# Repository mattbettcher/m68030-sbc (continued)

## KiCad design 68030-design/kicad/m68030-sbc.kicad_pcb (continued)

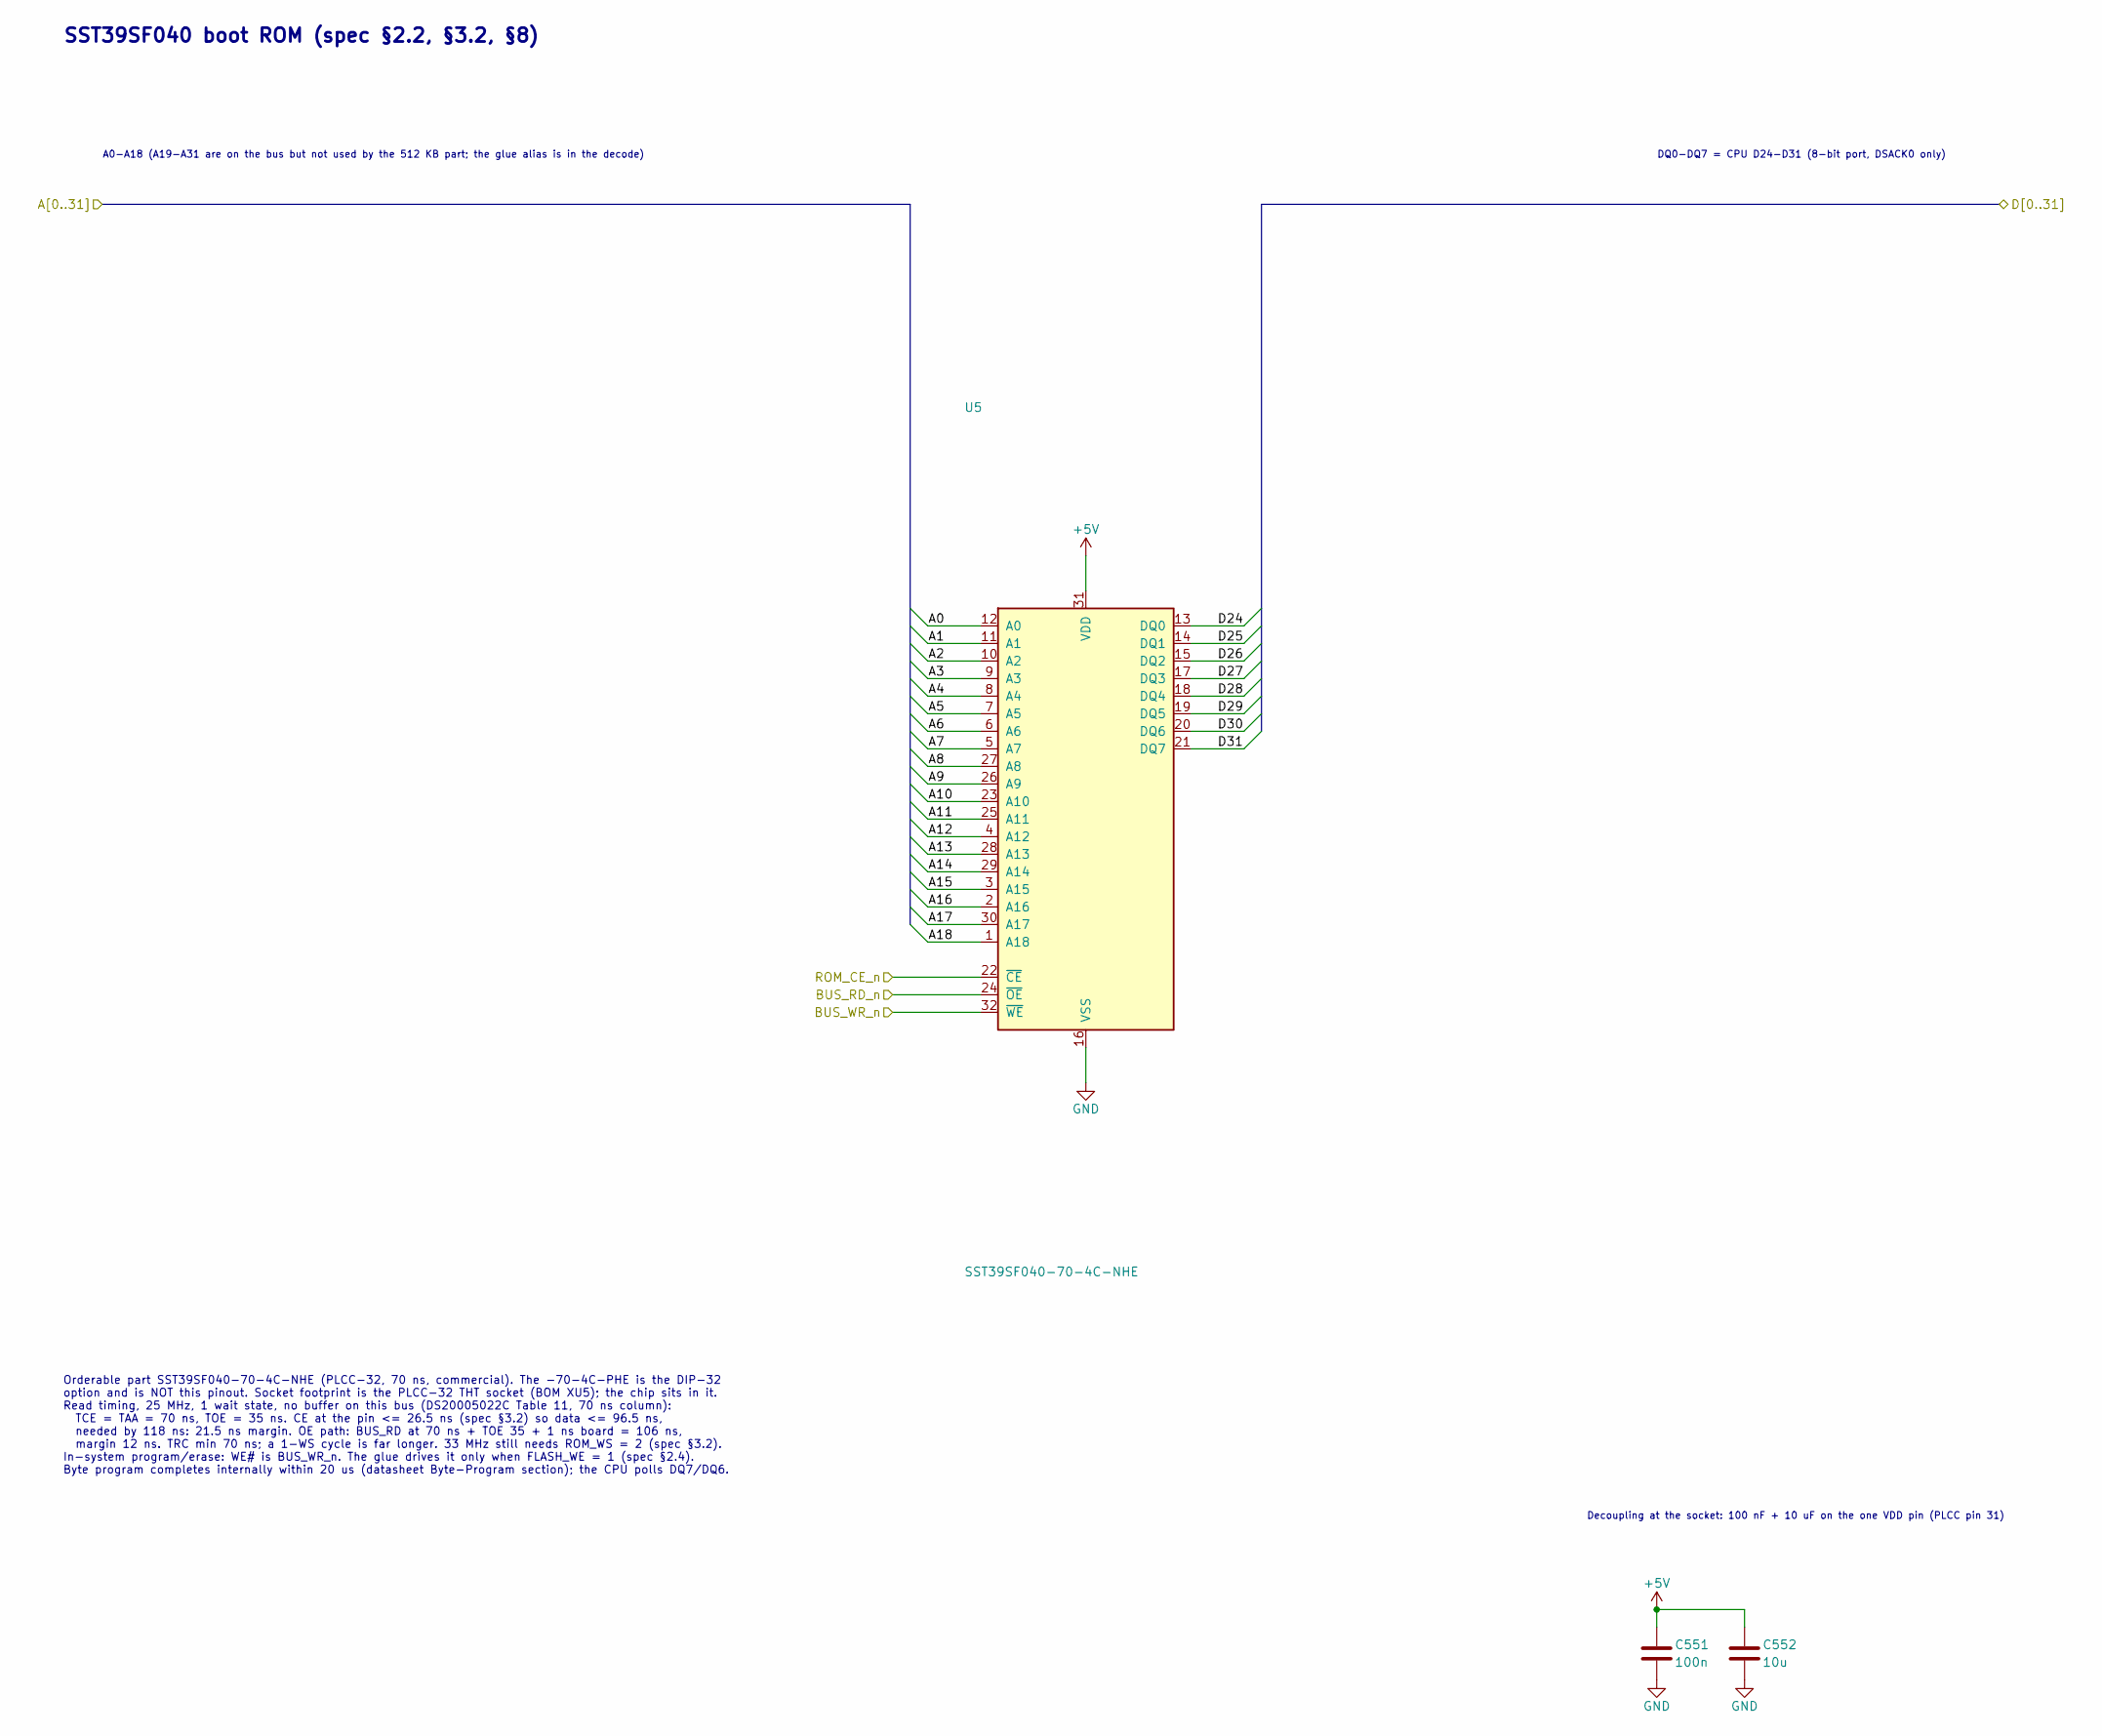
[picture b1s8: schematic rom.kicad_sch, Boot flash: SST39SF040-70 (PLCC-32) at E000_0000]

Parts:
C551: 100n; C_0805_2012Metric
C552: 10u; C_1206_3216Metric
U5: SST39SF040-70-4C-NHE; PLCC-32_THT-Socket; MPN SST39SF040-70-4C-NHE

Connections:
+5V: C551.1, C552.1, U5.31 (VDD); also elsewhere on the board
/A0: U5.12 (A0); also elsewhere on the board
/A1: U5.11 (A1); also elsewhere on the board
/A2: U5.10 (A2); also elsewhere on the board
/A3: U5.9 (A3); also elsewhere on the board
/A4: U5.8 (A4); also elsewhere on the board
/A5: U5.7 (A5); also elsewhere on the board
/A6: U5.6 (A6); also elsewhere on the board
/A7: U5.5 (A7); also elsewhere on the board
/A8: U5.27 (A8); also elsewhere on the board
/A9: U5.26 (A9); also elsewhere on the board
/A10: U5.23 (A10); also elsewhere on the board
/A11: U5.25 (A11); also elsewhere on the board
/A12: U5.4 (A12); also elsewhere on the board
/A13: U5.28 (A13); also elsewhere on the board
/A14: U5.29 (A14); also elsewhere on the board
/A15: U5.3 (A15); also elsewhere on the board
/A16: U5.2 (A16); also elsewhere on the board
/A17: U5.30 (A17); also elsewhere on the board
/A18: U5.1 (A18); also elsewhere on the board
/BUS_RD_n: U5.24 (~OE); also elsewhere on the board
/BUS_WR_n: U5.32 (~WE); also elsewhere on the board
/D24: U5.13 (DQ0); also elsewhere on the board
/D25: U5.14 (DQ1); also elsewhere on the board
/D26: U5.15 (DQ2); also elsewhere on the board
/D27: U5.17 (DQ3); also elsewhere on the board
/D28: U5.18 (DQ4); also elsewhere on the board
/D29: U5.19 (DQ5); also elsewhere on the board
/D30: U5.20 (DQ6); also elsewhere on the board
/D31: U5.21 (DQ7); also elsewhere on the board
/ROM_CE_n: U5.22 (~CE); also elsewhere on the board
GND: C551.2, C552.2, U5.16 (VSS); also elsewhere on the board

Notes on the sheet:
A0-A18 (A19-A31 are on the bus but not used by the 512 KB part; the glue alias is in the decode)
DQ0-DQ7 = CPU D24-D31 (8-bit port, DSACK0 only)
Decoupling at the socket: 100 nF + 10 uF on the one VDD pin (PLCC pin 31)
SST39SF040 boot ROM (spec §2.2, §3.2, §8)
Orderable part SST39SF040-70-4C-NHE (PLCC-32, 70 ns, commercial). The -70-4C-PHE is the DIP-32 option and is NOT this pinout. Socket footprint is the PLCC-32 THT socket (BOM XU5); the chip sits in it. Read timing, 25 MHz, 1 wait state, no buffer on this bus (DS20005022C Table 11, 70 ns column): TCE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

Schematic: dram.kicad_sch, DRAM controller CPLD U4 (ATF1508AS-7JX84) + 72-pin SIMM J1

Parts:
C801, C802, C803, C804, C805, C806, C807, C808, C810, C811, C812: 100n; C_0805_2012Metric
C809, C813, C814, C815: 10u; C_1206_3216Metric
C816, C817: 470u; CP_Radial_D10.0mm_P5.00mm
C818, C819, C820: 100n; C_0805_2012Metric; not fitted
J1: SIMM-72 socket; SIMM-72_TE-5822021-4; MPN TE 5822021-4
J5: JTAG U4 (ATDH1150USB); IDC-Header_2x05_P2.54mm_Vertical
JP801, JP802, JP803, JP804: open; SolderJumper-2_P1.3mm_Open_RoundedPad1.0x1.5mm
R801, R802, R803: 4.7k; R_0603_1608Metric
R804, R805, R806, R807, R808, R809, R810, R811, R812, R813, R814, R815, R816, R817, R818, R819, R820, R821, R822, R823, R824: 33; R_0603_1608Metric
R825, R826, R827, R828: 10k; R_0603_1608Metric
R829, R830, R831, R832, R833, R834, R835, R836, R837, R838: 33; R_0603_1608Metric; not fitted
TP801: RAS0#; TestPoint_Pad_D1.5mm
TP802: RAS1#; TestPoint_Pad_D1.5mm
TP803: CAS0#; TestPoint_Pad_D1.5mm
TP804: CAS1#; TestPoint_Pad_D1.5mm
TP805: CAS2#; TestPoint_Pad_D1.5mm
TP806: CAS3#; TestPoint_Pad_D1.5mm
TP807: WE#; TestPoint_Pad_D1.5mm
TP808: MUX_SEL; TestPoint_Pad_D1.5mm
TP809: U4-81; TestPoint_Pad_D1.5mm
U4: ATF1508AS-7JX84; PLCC-84_THT-Socket; MPN ATF1508AS-7JX84
U801, U802, U803: 74ACT257; SOIC-16_3.9x9.9mm_P1.27mm; MPN MC74ACT257DR2G; not fitted

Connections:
+5V: C801.1, C802.1, C803.1, C804.1, C805.1, C806.1, C807.1, C808.1, C809.1, C810.1, C811.1, C812.1, C813.1, C814.1, C815.1, C816.1, C817.1, C818.1, C819.1, C820.1, J1.10 (VDD), J1.30 (VDD), J1.59 (VDD), J5.4, R801.1, R802.1, R825.1, R826.1, R827.1, R828.1, U4.3 (VCCINT), U4.13 (VCCIO), U4.26 (VCCIO), U4.38 (VCCIO), U4.43 (VCCINT), U4.53 (VCCIO), U4.66 (VCCIO), U4.78 (VCCIO), U801.16 (VCC), U802.16 (VCC), U803.16 (VCC); also elsewhere on the board
/A0: U4.34 (I/O); also elsewhere on the board
/A1: U4.37 (I/O); also elsewhere on the board
/A2: U4.60 (I/O); also elsewhere on the board
/A3: U4.64 (I/O); also elsewhere on the board
/A4: U4.58 (I/O), U801.3 (I1a); also elsewhere on the board
/A5: U4.68 (I/O), U801.6 (I1b); also elsewhere on the board
/A6: U4.61 (I/O), U801.13 (I1c); also elsewhere on the board
/A7: U4.56 (I/O), U801.10 (I1d); also elsewhere on the board
/A8: U4.57 (I/O), U802.3 (I1a); also elsewhere on the board
/A9: U4.63 (I/O), U802.6 (I1b); also elsewhere on the board
/A10: U4.54 (I/O), U802.13 (I1c); also elsewhere on the board
/A11: U4.51 (I/O), U802.10 (I1d); also elsewhere on the board
/A12: U4.65 (I/O); also elsewhere on the board
/A13: U4.55 (I/O); also elsewhere on the board
/A14: U4.69 (I/O), U801.2 (I0a); also elsewhere on the board
/A15: U4.67 (I/O), U801.5 (I0b); also elsewhere on the board
/A16: U4.73 (I/O), U801.14 (I0c); also elsewhere on the board
/A17: U4.52 (I/O), U801.11 (I0d); also elsewhere on the board
/A18: U4.48 (I/O), U802.2 (I0a); also elsewhere on the board
/A19: U4.49 (I/O), U802.5 (I0b); also elsewhere on the board
/A20: U4.80 (I/O), U802.14 (I0c); also elsewhere on the board
/A21: U4.45 (I/O/PD2), U802.11 (I0d); also elsewhere on the board
/A22: U4.46 (I/O), U803.2 (I0a); also elsewhere on the board
/A23: U4.44 (I/O), U803.3 (I1a); also elsewhere on the board
/A24: U4.41 (I/O), U803.5 (I0b); also elsewhere on the board
/A25: U4.40 (I/O), U803.6 (I1b); also elsewhere on the board
/A26: U4.39 (I/O); also elsewhere on the board
/AS_n: U4.84 (INPUT/OE1); also elsewhere on the board
/CAS3_n: J1.42 (~CAS3), R823.2, TP806.1
/CBACK_n: JP803.1 (A); also elsewhere on the board
/CBREQ_n: JP802.1 (A); also elsewhere on the board
/CLK_DRAMC: U4.2 (INPUT/OE2/GCLK2); also elsewhere on the board
/D0: J1.2 (DQ1); also elsewhere on the board
/D1: J1.4 (DQ2); also elsewhere on the board
/D2: J1.6 (DQ3); also elsewhere on the board
/D3: J1.8 (DQ4); also elsewhere on the board
/D4: J1.20 (DQ5); also elsewhere on the board
/D5: J1.22 (DQ6); also elsewhere on the board
/D6: J1.24 (DQ7); also elsewhere on the board
/D7: J1.26 (DQ8); also elsewhere on the board
/D8: J1.49 (DQ9); also elsewhere on the board
/D9: J1.51 (DQ10); also elsewhere on the board
/D10: J1.53 (DQ11); also elsewhere on the board
/D11: J1.55 (DQ12); also elsewhere on the board
/D12: J1.57 (DQ13); also elsewhere on the board
/D13: J1.61 (DQ14); also elsewhere on the board
/D14: J1.63 (DQ15); also elsewhere on the board
/D15: J1.65 (DQ16); also elsewhere on the board
/D16: J1.3 (DQ17); also elsewhere on the board
/D17: J1.5 (DQ18); also elsewhere on the board
/D18: J1.7 (DQ19); also elsewhere on the board
/D19: J1.9 (DQ20); also elsewhere on the board
/D20: J1.21 (DQ21); also elsewhere on the board
/D21: J1.23 (DQ22); also elsewhere on the board
/D22: J1.25 (DQ23); also elsewhere on the board
/D23: J1.27 (DQ24); also elsewhere on the board
/D24: J1.50 (DQ25); also elsewhere on the board
/D25: J1.52 (DQ26); also elsewhere on the board
/D26: J1.54 (DQ27); also elsewhere on the board
/D27: J1.56 (DQ28); also elsewhere on the board
/D28: J1.58 (DQ29); also elsewhere on the board
/D29: J1.60 (DQ30); also elsewhere on the board
/D30: J1.62 (DQ31); also elsewhere on the board
/D31: J1.64 (DQ32); also elsewhere on the board
/DRAM_CLK: U4.83 (INPUT/GCLK1); also elsewhere on the board
/DRAM_SEL_n: U4.33 (I/O); also elsewhere on the board
/DSACK0_n: U4.28 (I/O); also elsewhere on the board
/DSACK1_n: U4.30 (I/O); also elsewhere on the board
/DS_n: JP804.2 (B); also elsewhere on the board
/PWR_RST_n: U4.1 (INPUT/GCLR); also elsewhere on the board
/RAS0_n: J1.44 (~RAS0), R816.2, TP801.1
/R_W: U4.31 (I/O); also elsewhere on the board
/SIMM_PD1: J1.67 (PRD1), R825.2; also elsewhere on the board
/SIMM_PD2: J1.68 (PRD2), R826.2; also elsewhere on the board
/SIMM_PD3: J1.69 (PRD3), R827.2; also elsewhere on the board
/SIMM_PD4: J1.70 (PRD4), R828.2; also elsewhere on the board
/SIZ0: U4.36 (I/O); also elsewhere on the board
/SIZ1: U4.35 (I/O); also elsewhere on the board
/STERM_n: JP801.1 (A); also elsewhere on the board
/WE_n: J1.47 (~WE), R824.2, TP807.1
/dram/CAS0_n: J1.40 (~CAS0), R820.2, TP803.1
/dram/CAS1_n: J1.43 (~CAS1), R821.2, TP804.1
/dram/CAS2_n: J1.41 (~CAS2), R822.2, TP805.1
/dram/MA0: J1.12 (A0), R804.2
/dram/MA1: J1.13 (A1), R805.2
/dram/MA2: J1.14 (A2), R806.2, R829.2
/dram/MA3: J1.15 (A3), R807.2, R830.2
/dram/MA4: J1.16 (A4), R808.2, R831.2
/dram/MA5: J1.17 (A5), R809.2, R832.2
/dram/MA6: J1.18 (A6), R810.2, R833.2
/dram/MA7: J1.28 (A7), R811.2, R834.2
/dram/MA8: J1.31 (A8), R812.2, R835.2
/dram/MA9: J1.32 (A9), R813.2, R836.2
/dram/MA10: J1.19 (A10), R814.2, R837.2
/dram/MA11: J1.29 (A11), R815.2, R838.2
/dram/MUX_SEL: TP808.1, U4.74 (I/O), U801.1 (S), U802.1 (S), U803.1 (S)
/dram/RAS1_n: J1.45 (~RAS1), R817.2, TP802.1
/dram/RAS2_n: J1.34 (~RAS2), R818.2
/dram/RAS3_n: J1.33 (~RAS3), R819.2
/dram/U4_CAS0_n: R820.1, U4.4 (I/O)
/dram/U4_CAS1_n: R821.1, U4.77 (I/O)
/dram/U4_CAS2_n: R822.1, U4.70 (I/O)
/dram/U4_CAS3_n: R823.1, U4.79 (I/O)
/dram/U4_MA0: R804.1, U4.22 (I/O)
/dram/U4_MA1: R805.1, U4.20 (I/O)
/dram/U4_MA2: R806.1, U4.25 (I/O)
/dram/U4_MA3: R807.1, U4.21 (I/O)
/dram/U4_MA4: R808.1, U4.24 (I/O)
/dram/U4_MA5: R809.1, U4.15 (I/O)
/dram/U4_MA6: R810.1, U4.12 (I/O/PD1)
/dram/U4_MA7: R811.1, U4.11 (I/O)
/dram/U4_MA8: R812.1, U4.27 (I/O)
/dram/U4_MA9: R813.1, U4.29 (I/O)
/dram/U4_MA10: R814.1, U4.10 (I/O)
/dram/U4_MA11: R815.1, U4.9 (I/O)
/dram/U4_RAS0_n: R816.1, U4.76 (I/O)
/dram/U4_RAS1_n: R817.1, U4.5 (I/O)
/dram/U4_RAS2_n: R818.1, U4.6 (I/O)
/dram/U4_RAS3_n: R819.1, U4.8 (I/O)
/dram/U4_SPARE81: TP809.1, U4.81 (I/O/GCLK3)
/dram/U4_TCK: J5.1, R803.1, U4.62 (I/O/TCK)
/dram/U4_TDI: J5.9, R802.2, U4.14 (I/O/TDI)
/dram/U4_TDO: J5.3, U4.71 (I/O/TDO)
/dram/U4_TMS: J5.5, R801.2, U4.23 (I/O/TMS)
/dram/U4_WE_n: R824.1, U4.75 (I/O)
GND: C801.2, C802.2, C803.2, C804.2, C805.2, C806.2, C807.2, C808.2, C809.2, C810.2, C811.2, C812.2, C813.2, C814.2, C815.2, C816.2, C817.2, C818.2, C819.2, C820.2, J1.1 (VSS), J1.39 (VSS), J1.72 (VSS), J5.2, J5.10, R803.2, U4.7 (GND), U4.19 (GND), U4.32 (GND), U4.42 (GND), U4.47 (GND), U4.59 (GND), U4.72 (GND), U4.82 (GND), U801.8 (GND), U801.15 (OE), U802.8 (GND), U802.15 (OE), U803.8 (GND), U803.10 (I1d), U803.11 (I0d), U803.13 (I1c), U803.14 (I0c), U803.15 (OE); also elsewhere on the board
unnamed: JP801.2 (B), U4.16 (I/O)
unnamed: JP802.2 (B), U4.17 (I/O)
unnamed: JP803.2 (B), U4.18 (I/O)
unnamed: JP804.1 (A), U4.50 (I/O)
unnamed: R829.1, U801.4 (Za)
unnamed: R830.1, U801.7 (Zb)
unnamed: R831.1, U801.12 (Zc)
unnamed: R832.1, U801.9 (Zd)
unnamed: R833.1, U802.4 (Za)
unnamed: R834.1, U802.7 (Zb)
unnamed: R835.1, U802.12 (Zc)
unnamed: R836.1, U802.9 (Zd)
unnamed: R837.1, U803.4 (Za)
unnamed: R838.1, U803.7 (Zb)

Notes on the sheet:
U4 address inputs A0-A26 are labelled A<n> (members of bus A[0..31])
U4 decoupling: 8x 100 nF, one at each VCC pin (VCCINT 3, 43; VCCIO 13, 26, 38, 53, 66, 78), + 10 uF bulk
Series terminations at U4 (spec 5.8)
33R, placed next to U4 (source termination)
R806-R815 (MA2-MA11): remove if the 74ACT257 fallback (U801-U803) is fitted
DQ1-DQ8 = D0-D7 (CAS0), DQ9-16 = D8-15 (CAS1), DQ17-24 = D16-23 (CAS2), DQ25-32 = D24-31 (CAS3)
SIMM presence detect (spec 5.1): 10k pull-ups; module ties PRDn to VSS or leaves it open. Read on DUART IP3-IP6 (advisory; firmware sizes by probing)
SIMM decoupling (spec 6.3): 100 nF + 10 uF at each VDD pin (10, 30, 59), 2x 470 uF low-ESR at the socket ends for the CBR refresh current spikes (all 16/32 DRAMs refresh at once)
Test points (SIMM side of the series resistors)
JTAG ISP header
J5: separate header for U4 (same pinout as J4 on the glue sheet; ATDH1150USB UG Table 1). Not chained with U3: the ATDH1150USB/ATMISP support multi-device chains, but a separate header lets each CPLD be programmed/recovered alone and a blank or damaged part cannot break the other's chain. R801/R802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
Fallback: external row/column address muxes (DNP)
Not needed: U4 fits with the MA mux inside (80/128 MC, 50 MHz met). To use: fit U801-U803 + C818-C820 and R829-R838, remove R806-R815 (U4 MA2-MA11 path), and rebuild dram.v with MA2-MA11 unused. S = MUX_SEL (U4 pin 74; low = row on I0, high = column on I1). 74ACT257 tpd <= 10.5 ns (onsemi MC74ACT25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
U801-U803 decoupling (DNP)
U4 DRAM controller + 72-pin SIMM (spec 3.2, 4.3, 5)
FITTED PINOUT: Yosys + hoglet67/atf15xx_yosys -> Microchip fit1508.exe v1918 (Wine), ATF1508AS PLCC84 -7, JTAG ON, pins locked (-preassign keep), -optimize on, -pin_keep on. Result: 80/128 macrocells, 52 flip-flops, 210 product terms; 55/60 user I/O + 4 JTAG + 3/4 dedicated inputs. Worst register-t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
Series resistors: 33R source termination on MA/RAS/CAS/WE. Trace Z0 ~50-60R minus the CPLD output impedance (~15-25R) [EST]; SIMM input loads (Micron): MA 48/95 pF, WE 64/127 pF, RAS 32 pF, CAS 16/32 pF (1/2-sided) -> 33R x 100 pF ~ 3.3 ns edge slowing, inside the DRAM timing margins (tRAH/tASC/tCA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

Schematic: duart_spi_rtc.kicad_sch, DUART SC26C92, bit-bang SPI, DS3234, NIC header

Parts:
BT1: CR2032; BatteryHolder_Keystone_3034_1x20mm; MPN Keystone 3034
C1001: 100n; C_0805_2012Metric
C1002: 10u; C_1206_3216Metric
C1003, C1004: 100n; C_0603_1608Metric
D6: OP6; LED_0805_2012Metric
J7, J8: TTL-232; PinHeader_1x06_P2.54mm_Vertical
J9: SPI NIC; PinHeader_2x05_P2.54mm_Vertical
R1001: 4.7k; R_0603_1608Metric
R1002, R1003, R1004, R1008: 10k; R_0603_1608Metric
R1005: 1.0k; R_0603_1608Metric
R1006: 2.2k; R_0603_1608Metric
R1007: 1k; R_0603_1608Metric
TP1001: OP7; TestPoint_Pad_D1.5mm
TP1002: RTC_INT; TestPoint_Pad_D1.5mm
U6: SC26C92A1A; PLCC-44_THT-Socket; MPN SC26C92A1A
U22: SN74LVC125ADR; SOIC-14_3.9x8.7mm_P1.27mm; MPN SN74LVC125ADR
U23: DS3234S#; SOIC-20W_7.5x12.8mm_P1.27mm; MPN DS3234S#

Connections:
+3V3: C1003.1, C1004.1, J9.1, R1004.1, R1008.1, U22.14 (VCC), U23.4 (VCC); also elsewhere on the board
+5V: C1001.1, C1002.1, J9.2, R1001.2, R1002.1, R1003.1, R1007.2, U6.44 (VCC); also elsewhere on the board
/A0: U6.2 (A0); also elsewhere on the board
/A1: U6.4 (A1); also elsewhere on the board
/A2: U6.6 (A2); also elsewhere on the board
/A3: U6.7 (A3); also elsewhere on the board
/BUS_RD_n: U6.10 (~RDN); also elsewhere on the board
/BUS_WR_n: U6.9 (~WRN); also elsewhere on the board
/D24: U6.28 (D0); also elsewhere on the board
/D25: U6.18 (D1); also elsewhere on the board
/D26: U6.27 (D2); also elsewhere on the board
/D27: U6.19 (D3); also elsewhere on the board
/D28: U6.26 (D4); also elsewhere on the board
/D29: U6.20 (D5); also elsewhere on the board
/D30: U6.25 (D6); also elsewhere on the board
/D31: U6.21 (D7); also elsewhere on the board
/DUART_CS_n: U6.39 (~CEN); also elsewhere on the board
/DUART_INT_n: R1001.1, U6.24 (~INTRN); also elsewhere on the board
/DUART_RST: U6.38 (RESET); also elsewhere on the board
/DUART_X1: U6.36 (X1); also elsewhere on the board
/DUART_X2: U6.37 (X2); also elsewhere on the board
/NIC_INT_n: J9.8, R1004.2; also elsewhere on the board
/PERIPH_RST_n: R1005.1; also elsewhere on the board
/SIMM_PD1: U6.3 (IP3); also elsewhere on the board
/SIMM_PD2: U6.43 (IP4); also elsewhere on the board
/SIMM_PD3: U6.42 (IP5); also elsewhere on the board
/SIMM_PD4: U6.41 (IP6); also elsewhere on the board
/SPI_HW_MISO: J9.6, U6.40 (IP2), U23.19 (DOUT); also elsewhere on the board
/SPI_HW_MOSI: U6.15 (OP3), U22.5; also elsewhere on the board
/SPI_HW_SCK: U6.31 (OP2), U22.2; also elsewhere on the board
/duart_spi_rtc/CTSA: J7.6, U6.8 (IP0)
/duart_spi_rtc/CTSB: J8.6, U6.5 (IP1)
/duart_spi_rtc/NIC_RST: J9.9, R1005.2, R1006.1
/duart_spi_rtc/OP6: D6.1 (K), U6.29 (OP6)
/duart_spi_rtc/OP7: TP1001.1, U6.17 (OP7)
/duart_spi_rtc/RTC_INT: R1008.2, TP1002.1, U23.5 (INT/SQW)
/duart_spi_rtc/RTSA: J7.2, U6.32 (OP0)
/duart_spi_rtc/RTSB: J8.2, U6.14 (OP1)
/duart_spi_rtc/RXDA: J7.4, U6.35 (RxDA)
/duart_spi_rtc/RXDB: J8.4, U6.11 (RxDB)
/duart_spi_rtc/SPI_CS0_5: R1002.2, U6.30 (OP4), U22.9
/duart_spi_rtc/SPI_CS1_5: R1003.2, U6.16 (OP5), U22.12
/duart_spi_rtc/SPI_CS_NIC: J9.7, U22.8
/duart_spi_rtc/SPI_CS_RTC: U22.11, U23.1 (~CS)
/duart_spi_rtc/SPI_MOSI: J9.5, U22.6, U23.17 (DIN)
/duart_spi_rtc/SPI_SCK: J9.4, U22.3, U23.18 (SCLK), U23.20 (SCLK)
/duart_spi_rtc/TXDA: J7.5, U6.33 (TxDA)
/duart_spi_rtc/TXDB: J8.5, U6.13 (TxDB)
/duart_spi_rtc/VBAT: BT1.1 (+), U23.16 (VBAT)
GND: BT1.2 (-), C1001.2, C1002.2, C1003.2, C1004.2, J7.1, J8.1, J9.3, J9.10, R1006.2, U6.22 (VSS), U22.1, U22.4, U22.7 (GND), U22.10, U22.13, U23.2 (NC), U23.7 (NC), U23.8 (NC), U23.9 (NC), U23.10 (NC), U23.11 (NC), U23.12 (NC), U23.13 (NC), U23.14 (NC), U23.15 (GND); also elsewhere on the board
unnamed: D6.2 (A), R1007.1

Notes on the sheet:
A0-A3 only (reg_shift = 0)
D0-D7 = CPU D24-D31
U6 decoupling (one VCC pin, PLCC pin 44)
SC26C92A1A (spec §8.3). Kept. 2 wait states still hold; glue not refit.
J7/J8 TTL-232: 1 GND, 2 CTS from our RTS, 3 cable VCC left open, 4 TXD to our RX, 5 RXD from our TX, 6 RTS to our CTS.
J9 pins: 1 +3V3, 2 +5V, 3 GND, 4 SCK, 5 MOSI, 6 MISO, 7 CS, 8 INT, 9 RST, 10 GND. SPI is 3.3 V.

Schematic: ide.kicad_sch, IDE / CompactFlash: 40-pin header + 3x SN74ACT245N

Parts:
C911, C912, C913: 100n; C_0805_2012Metric
D5: IDE; LED_0805_2012Metric
J6: IDE 40-pin; IDC-Header_2x20_P2.54mm_Vertical; MPN Wurth 61204021621
R901: 4.7k; R_0603_1608Metric
R902, R903, R905: 10k; R_0603_1608Metric
R904: 5.6k; R_0603_1608Metric
R906: 1k; R_0603_1608Metric
R911, R912, R913, R914, R915, R916, R917, R918: 33; R_0603_1608Metric
U11, U12, U13: SN74ACT245DW; SOIC-20W_7.5x12.8mm_P1.27mm; MPN SN74ACT245DW

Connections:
+5V: C911.1, C912.1, C913.1, R901.1, R905.1, R906.2, U11.20 (VCC), U12.20 (VCC), U13.1 (A->B), U13.20 (VCC); also elsewhere on the board
/D16: U12.18 (B0); also elsewhere on the board
/D17: U12.17 (B1); also elsewhere on the board
/D18: U12.16 (B2); also elsewhere on the board
/D19: U12.15 (B3); also elsewhere on the board
/D20: U12.14 (B4); also elsewhere on the board
/D21: U12.13 (B5); also elsewhere on the board
/D22: U12.12 (B6); also elsewhere on the board
/D23: U12.11 (B7); also elsewhere on the board
/D24: U11.18 (B0); also elsewhere on the board
/D25: U11.17 (B1); also elsewhere on the board
/D26: U11.16 (B2); also elsewhere on the board
/D27: U11.15 (B3); also elsewhere on the board
/D28: U11.14 (B4); also elsewhere on the board
/D29: U11.13 (B5); also elsewhere on the board
/D30: U11.12 (B6); also elsewhere on the board
/D31: U11.11 (B7); also elsewhere on the board
/IDE_BUF_EN_n: U11.19 (CE), U12.19 (CE); also elsewhere on the board
/IDE_CS0_n: U13.5 (A3); also elsewhere on the board
/IDE_CS1_n: U13.6 (A4); also elsewhere on the board
/IDE_DA0: U13.2 (A0); also elsewhere on the board
/IDE_DA1: U13.3 (A1); also elsewhere on the board
/IDE_DA2: U13.4 (A2); also elsewhere on the board
/IDE_DIOR_n: U13.7 (A5); also elsewhere on the board
/IDE_DIOW_n: U13.8 (A6); also elsewhere on the board
/IDE_INTRQ: J6.31, R903.1; also elsewhere on the board
/IDE_IORDY: J6.27, R901.2; also elsewhere on the board
/PERIPH_RST_n: U13.9 (A7); also elsewhere on the board
/R_W: U11.1 (A->B), U12.1 (A->B); also elsewhere on the board
/ide/CS0_n: J6.37, R914.2
/ide/CS1_n: J6.38, R915.2
/ide/DA0: J6.35, R911.2
/ide/DA1: J6.33, R912.2
/ide/DA2: J6.36, R913.2
/ide/DASP_n: D5.1 (K), J6.39
/ide/DD0: J6.17, U11.2 (A0)
/ide/DD1: J6.15, U11.3 (A1)
/ide/DD2: J6.13, U11.4 (A2)
/ide/DD3: J6.11, U11.5 (A3)
/ide/DD4: J6.9, U11.6 (A4)
/ide/DD5: J6.7, U11.7 (A5)
/ide/DD6: J6.5, U11.8 (A6)
/ide/DD7: J6.3, R902.1, U11.9 (A7)
/ide/DD8: J6.4, U12.2 (A0)
/ide/DD9: J6.6, U12.3 (A1)
/ide/DD10: J6.8, U12.4 (A2)
/ide/DD11: J6.10, U12.5 (A3)
/ide/DD12: J6.12, U12.6 (A4)
/ide/DD13: J6.14, U12.7 (A5)
/ide/DD14: J6.16, U12.8 (A6)
/ide/DD15: J6.18, U12.9 (A7)
/ide/DIOR_n: J6.25, R916.2
/ide/DIOW_n: J6.23, R917.2
/ide/DMACK_n: J6.29, R905.2
/ide/DMARQ: J6.21, R904.1
/ide/RESET_n: J6.1, R918.2
GND: C911.2, C912.2, C913.2, J6.2, J6.19, J6.22, J6.24, J6.26, J6.28, J6.30, J6.40, R902.2, R903.2, R904.2, U11.10 (GND), U12.10 (GND), U13.10 (GND), U13.19 (CE); also elsewhere on the board
unnamed: D5.2 (A), R906.1
unnamed: R911.1, U13.18 (B0)
unnamed: R912.1, U13.17 (B1)
unnamed: R913.1, U13.16 (B2)
unnamed: R914.1, U13.15 (B3)
unnamed: R915.1, U13.14 (B4)
unnamed: R916.1, U13.13 (B5)
unnamed: R917.1, U13.12 (B6)
unnamed: R918.1, U13.11 (B7)

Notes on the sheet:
D24-D31 (U11) and D16-D23 (U12) are members of D[0..31]. DIR = R/W high drives DD onto the CPU.
U13 is wired one way: DIR = +5V (A->B), OE = GND. DA2:0 are U3 pins 50-52, registered (glue Rev A.1).
U11 / U12 / U13 decoupling
IDE header (spec §1.2, §3.2). A CF-to-40-pin adapter uses this connector; no separate CF socket.
Terminations, ATA/ATAPI-6 (T13/1410D) §4.2.1 Table 5, notes 3, 4, 5, 7, 10: R901 4.7k IORDY pull-up to +5V (table value; note 10 allows 1k, not used). R902 10k DD7 pull-down (note 3: host shall pull DD7 down, not up). R903 10k INTRQ pull-down (note 5; spec §3.5: active high). R904 5.6k DMARQ pull-d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
PIO-0 vs SN74ACT245N (SCAS452H Fig. 6-1, CL = 50 pF only; no 150 pF number). SN74, VCC 5 V +/- 0.5 V, over temperature: tPLH 1.5 to 8 ns, tPHL 1 to 9 ns. 13 WS unchanged. At the drive: t0 631 ns (margin 31), t1 111.7 (42), t2 352.5 (62 vs 290), t4 50 (20), t9 36.6 (17). Read t5 misses: DIOR tPLH an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

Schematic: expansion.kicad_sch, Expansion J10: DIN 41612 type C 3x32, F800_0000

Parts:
C1401, C1402, C1403, C1404, C1405, C1406, C1407, C1408: 100n; C_0805_2012Metric
C1409: 10u; C_1206_3216Metric
J10: DIN41612-C-96; DIN41612_C_3x32_Female_Vertical_THT; MPN HARTING 09032966821
U14, U15, U16, U17: SN74ACT244DW; SOIC-20W_7.5x12.8mm_P1.27mm; MPN SN74ACT244DW
U18, U19, U20, U21: SN74ACT245DW; SOIC-20W_7.5x12.8mm_P1.27mm; MPN SN74ACT245DW

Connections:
+5V: C1401.1, C1402.1, C1403.1, C1404.1, C1405.1, C1406.1, C1407.1, C1408.1, C1409.1, J10.c21, J10.c22, J10.c23, J10.c24, U14.20 (VCC), U15.20 (VCC), U16.20 (VCC), U17.20 (VCC), U18.20 (VCC), U19.20 (VCC), U20.20 (VCC), U21.20 (VCC); also elsewhere on the board
/A0: U14.2 (I0a); also elsewhere on the board
/A1: U14.4 (I1a); also elsewhere on the board
/A2: U14.6 (I2a); also elsewhere on the board
/A3: U14.8 (I3a); also elsewhere on the board
/A4: U14.11 (I0b); also elsewhere on the board
/A5: U14.13 (I1b); also elsewhere on the board
/A6: U14.15 (I2b); also elsewhere on the board
/A7: U14.17 (I3b); also elsewhere on the board
/A8: U15.2 (I0a); also elsewhere on the board
/A9: U15.4 (I1a); also elsewhere on the board
/A10: U15.6 (I2a); also elsewhere on the board
/A11: U15.8 (I3a); also elsewhere on the board
/A12: U15.11 (I0b); also elsewhere on the board
/A13: U15.13 (I1b); also elsewhere on the board
/A14: U15.15 (I2b); also elsewhere on the board
/A15: U15.17 (I3b); also elsewhere on the board
/A16: U16.2 (I0a); also elsewhere on the board
/A17: U16.4 (I1a); also elsewhere on the board
/A18: U16.6 (I2a); also elsewhere on the board
/A19: U16.8 (I3a); also elsewhere on the board
/A20: U16.11 (I0b); also elsewhere on the board
/A21: U16.13 (I1b); also elsewhere on the board
/A22: U16.15 (I2b); also elsewhere on the board
/A23: U16.17 (I3b); also elsewhere on the board
/AS_n: U17.15 (I2b); also elsewhere on the board
/BERR_n: J10.c9; also elsewhere on the board
/BGACK_n: J10.c6; also elsewhere on the board
/BG_n: J10.c4; also elsewhere on the board
/BR_n: J10.c5; also elsewhere on the board
/CLK_EXP: J10.c1; also elsewhere on the board
/D0: U18.18 (B0); also elsewhere on the board
/D1: U18.17 (B1); also elsewhere on the board
/D2: U18.16 (B2); also elsewhere on the board
/D3: U18.15 (B3); also elsewhere on the board
/D4: U18.14 (B4); also elsewhere on the board
/D5: U18.13 (B5); also elsewhere on the board
/D6: U18.12 (B6); also elsewhere on the board
/D7: U18.11 (B7); also elsewhere on the board
/D8: U19.18 (B0); also elsewhere on the board
/D9: U19.17 (B1); also elsewhere on the board
/D10: U19.16 (B2); also elsewhere on the board
/D11: U19.15 (B3); also elsewhere on the board
/D12: U19.14 (B4); also elsewhere on the board
/D13: U19.13 (B5); also elsewhere on the board
/D14: U19.12 (B6); also elsewhere on the board
/D15: U19.11 (B7); also elsewhere on the board
/D16: U20.18 (B0); also elsewhere on the board
/D17: U20.17 (B1); also elsewhere on the board
/D18: U20.16 (B2); also elsewhere on the board
/D19: U20.15 (B3); also elsewhere on the board
/D20: U20.14 (B4); also elsewhere on the board
/D21: U20.13 (B5); also elsewhere on the board
/D22: U20.12 (B6); also elsewhere on the board
/D23: U20.11 (B7); also elsewhere on the board
/D24: U21.18 (B0); also elsewhere on the board
/D25: U21.17 (B1); also elsewhere on the board
/D26: U21.16 (B2); also elsewhere on the board
/D27: U21.15 (B3); also elsewhere on the board
/D28: U21.14 (B4); also elsewhere on the board
/D29: U21.13 (B5); also elsewhere on the board
/D30: U21.12 (B6); also elsewhere on the board
/D31: U21.11 (B7); also elsewhere on the board
/DSACK0_n: J10.c7; also elsewhere on the board
/DSACK1_n: J10.c8; also elsewhere on the board
/DS_n: U17.17 (I3b); also elsewhere on the board
/EXP_BUF_EN_n: U18.19 (CE), U19.19 (CE), U20.19 (CE), U21.19 (CE); also elsewhere on the board
/EXP_INT_n: J10.c11; also elsewhere on the board
/EXP_SEL_n: J10.c2; also elsewhere on the board
/FC0: U17.6 (I2a); also elsewhere on the board
/FC1: U17.8 (I3a); also elsewhere on the board
/FC2: U17.11 (I0b); also elsewhere on the board
/HALT_n: J10.c10; also elsewhere on the board
/PERIPH_RST_n: J10.c3; also elsewhere on the board
/R_W: U17.13 (I1b), U18.1 (A->B), U19.1 (A->B), U20.1 (A->B), U21.1 (A->B); also elsewhere on the board
/SIZ0: U17.2 (I0a); also elsewhere on the board
/SIZ1: U17.4 (I1a); also elsewhere on the board
/expansion/J10_A0: J10.a1, U14.18 (O0a)
/expansion/J10_A1: J10.a2, U14.16 (O1a)
/expansion/J10_A2: J10.a3, U14.14 (O2a)
/expansion/J10_A3: J10.a4, U14.12 (O3a)
/expansion/J10_A4: J10.a5, U14.9 (O0b)
/expansion/J10_A5: J10.a6, U14.7 (O1b)
/expansion/J10_A6: J10.a7, U14.5 (O2b)
/expansion/J10_A7: J10.a8, U14.3 (O3b)
/expansion/J10_A8: J10.a9, U15.18 (O0a)
/expansion/J10_A9: J10.a10, U15.16 (O1a)
/expansion/J10_A10: J10.a11, U15.14 (O2a)
/expansion/J10_A11: J10.a12, U15.12 (O3a)
/expansion/J10_A12: J10.a13, U15.9 (O0b)
/expansion/J10_A13: J10.a14, U15.7 (O1b)
/expansion/J10_A14: J10.a15, U15.5 (O2b)
/expansion/J10_A15: J10.a16, U15.3 (O3b)
/expansion/J10_A16: J10.a17, U16.18 (O0a)
/expansion/J10_A17: J10.a18, U16.16 (O1a)
/expansion/J10_A18: J10.a19, U16.14 (O2a)
/expansion/J10_A19: J10.a20, U16.12 (O3a)
/expansion/J10_A20: J10.a21, U16.9 (O0b)
/expansion/J10_A21: J10.a22, U16.7 (O1b)
/expansion/J10_A22: J10.a23, U16.5 (O2b)
/expansion/J10_A23: J10.a24, U16.3 (O3b)
/expansion/J10_AS_n: J10.a31, U17.5 (O2b)
/expansion/J10_D0: J10.b1, U18.2 (A0)
/expansion/J10_D1: J10.b2, U18.3 (A1)
/expansion/J10_D2: J10.b3, U18.4 (A2)
/expansion/J10_D3: J10.b4, U18.5 (A3)
/expansion/J10_D4: J10.b5, U18.6 (A4)
/expansion/J10_D5: J10.b6, U18.7 (A5)
/expansion/J10_D6: J10.b7, U18.8 (A6)
/expansion/J10_D7: J10.b8, U18.9 (A7)
/expansion/J10_D8: J10.b9, U19.2 (A0)
/expansion/J10_D9: J10.b10, U19.3 (A1)
/expansion/J10_D10: J10.b11, U19.4 (A2)
/expansion/J10_D11: J10.b12, U19.5 (A3)
/expansion/J10_D12: J10.b13, U19.6 (A4)
/expansion/J10_D13: J10.b14, U19.7 (A5)
/expansion/J10_D14: J10.b15, U19.8 (A6)
/expansion/J10_D15: J10.b16, U19.9 (A7)
/expansion/J10_D16: J10.b17, U20.2 (A0)
/expansion/J10_D17: J10.b18, U20.3 (A1)
/expansion/J10_D18: J10.b19, U20.4 (A2)
/expansion/J10_D19: J10.b20, U20.5 (A3)
/expansion/J10_D20: J10.b21, U20.6 (A4)
/expansion/J10_D21: J10.b22, U20.7 (A5)
/expansion/J10_D22: J10.b23, U20.8 (A6)
/expansion/J10_D23: J10.b24, U20.9 (A7)
/expansion/J10_D24: J10.b25, U21.2 (A0)
/expansion/J10_D25: J10.b26, U21.3 (A1)
/expansion/J10_D26: J10.b27, U21.4 (A2)
/expansion/J10_D27: J10.b28, U21.5 (A3)
/expansion/J10_D28: J10.b29, U21.6 (A4)
/expansion/J10_D29: J10.b30, U21.7 (A5)
/expansion/J10_D30: J10.b31, U21.8 (A6)
/expansion/J10_D31: J10.b32, U21.9 (A7)
/expansion/J10_DS_n: J10.a32, U17.3 (O3b)
/expansion/J10_FC0: J10.a27, U17.14 (O2a)
/expansion/J10_FC1: J10.a28, U17.12 (O3a)
/expansion/J10_FC2: J10.a29, U17.9 (O0b)
/expansion/J10_R_W: J10.a30, U17.7 (O1b)
/expansion/J10_SIZ0: J10.a25, U17.18 (O0a)
/expansion/J10_SIZ1: J10.a26, U17.16 (O1a)
GND: C1401.2, C1402.2, C1403.2, C1404.2, C1405.2, C1406.2, C1407.2, C1408.2, C1409.2, J10.c12, J10.c13, J10.c14, J10.c15, J10.c16, J10.c17, J10.c18, J10.c19, J10.c20, U14.1 (OEa), U14.10 (GND), U14.19 (OEb), U15.1 (OEa), U15.10 (GND), U15.19 (OEb), U16.1 (OEa), U16.10 (GND), U16.19 (OEb), U17.1 (OEa), U17.10 (GND), U17.19 (OEb), U18.10 (GND), U19.10 (GND), U20.10 (GND), U21.10 (GND); also elsewhere on the board

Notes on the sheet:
A24-A31 are not buffered to J10. The card is selected by EXP_SEL_n (glue decode of F800_0000-FFFF_FFFF).
Decoupling: 100 nF at each of U14-U21, plus 10 uF for the group
J10 pinout (this sheet is the definition; spec §10 risk 18 had none)
Row a: a1-a24 = A0-A23, a25 SIZ0, a26 SIZ1, a27-a29 FC0-FC2, a30 R/W, a31 AS-, a32 DS- (all through U14-U17, 74ACT244, OE tied low so the card always sees the bus). Row b: b1-b32 = D0-D31 through U18-U21, 74ACT245. OE = EXP_BUF_EN_n (glue, active low). DIR = R/W with the card on the A side, so a CP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
